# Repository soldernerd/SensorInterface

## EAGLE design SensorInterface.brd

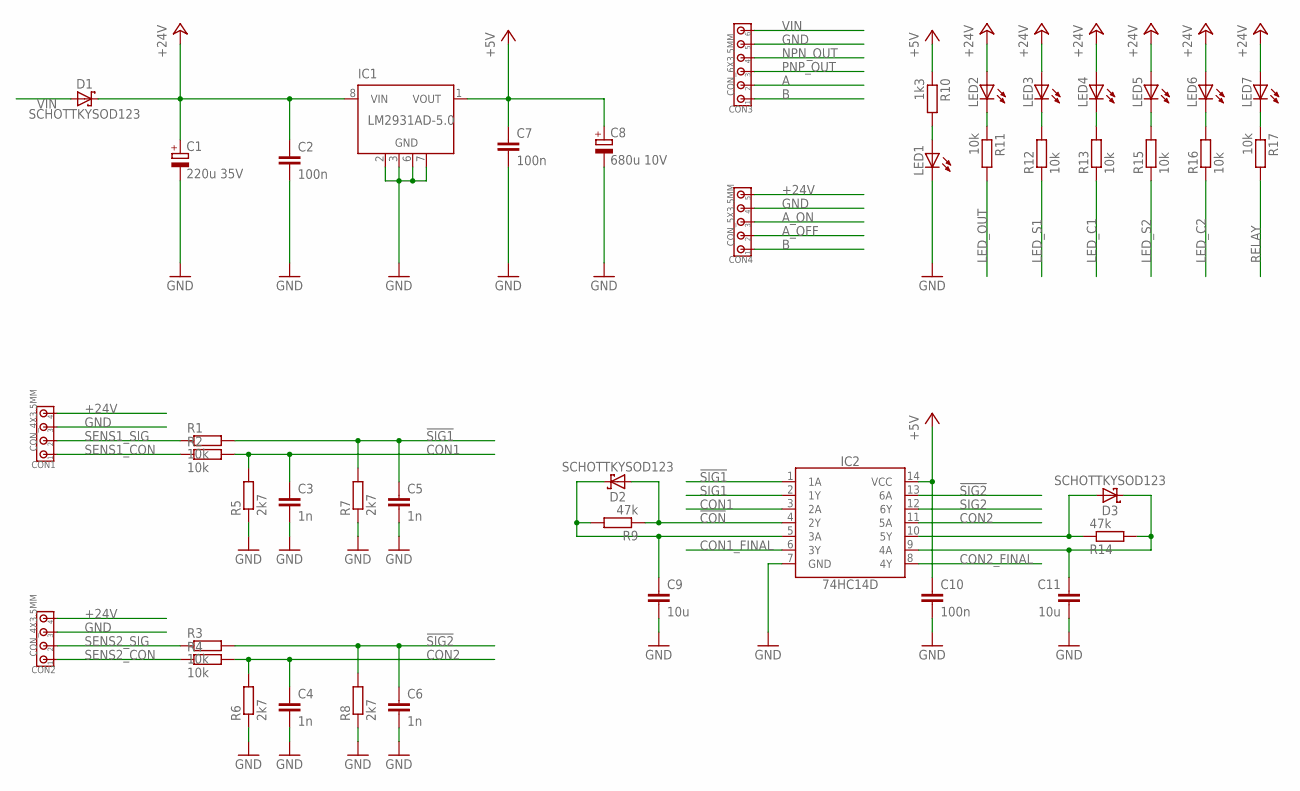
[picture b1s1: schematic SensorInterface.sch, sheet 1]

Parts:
C1: 220u 35V; 8MM
C2, C7, C10: 100n; C0805
C3, C4, C5, C6: 1n; C0805
C8: 680u 10V; 8MM
C9, C11: 10u; C0805
CON1, CON2: CON_4X3.5MM; 3.5MM_4X
CON3: CON_6X3.5MM; 3.5MM_6X
CON4: CON_5X3.5MM; 3.5MM_5X
D1, D2, D3: SCHOTTKYSOD123; SOD123
IC1: LM2931AD-5.0; SOIC8
IC2: 74HC14D; SO14
LED1, LED2, LED3, LED4, LED5, LED6, LED7: LED0805_NB; LED0805_NOBOARDER
R1, R2, R3, R4, R11, R12, R13, R15, R16, R17: 10k; R0805
R5, R6, R7, R8: 2k7; R0805
R9, R14: 47k; R0805
R10: 1k3; R0805

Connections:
!CON!: D2.A, IC2.4 (2Y), R9.1
!CON!1: D3.A, IC2.10 (5Y), R14.1
!SIG1!: C5.1, IC2.1 (1A), R1.2, R7.2; also elsewhere on the board
!SIG2!: C6.1, IC2.13 (6A), R3.2, R8.2; also elsewhere on the board
+5V: C7.1, C8.+, C10.1, IC1.1 (VOUT), IC2.14 (VCC), R10.1; also elsewhere on the board
+24V: C1.+, C2.1, CON1.4, CON2.4, CON4.5, D1.C, IC1.8 (VIN), LED2.A, LED3.A, LED4.A, LED5.A, LED6.A, LED7.A; also elsewhere on the board
A: CON3.2; also elsewhere on the board
A_OFF: CON4.2; also elsewhere on the board
A_ON: CON4.3; also elsewhere on the board
B: CON3.1, CON4.1
CON1: C3.1, IC2.3 (2A), R2.2, R5.2
CON1_FINAL: IC2.6 (3Y); also elsewhere on the board
CON2: C4.1, IC2.11 (5A), R4.2, R6.2
CON2_FINAL: IC2.8 (4Y); also elsewhere on the board
GND: C1.-, C2.2, C3.2, C4.2, C5.2, C6.2, C7.2, C8.-, C9.2, C10.2, C11.2, CON1.3, CON2.3, CON3.5, CON4.4, IC1.2 (GND), IC1.3 (GND), IC1.6 (GND), IC1.7 (GND), IC2.7 (GND), LED1.C, R5.1, R6.1, R7.1, R8.1; also elsewhere on the board
LED_C1: R13.1; also elsewhere on the board
LED_C2: R16.1; also elsewhere on the board
LED_OUT: R11.2; also elsewhere on the board
LED_S1: R12.1; also elsewhere on the board
LED_S2: R15.1; also elsewhere on the board
unnamed: C11.1, D3.C, IC2.9 (4A), R14.2
unnamed: C9.1, D2.C, IC2.5 (3A), R9.2
unnamed: LED1.A, R10.2
unnamed: LED2.C, R11.1
unnamed: LED7.C, R17.1
unnamed: LED6.C, R16.2
unnamed: LED5.C, R15.2
unnamed: LED4.C, R13.2
unnamed: LED3.C, R12.2
NPN_OUT: CON3.4; also elsewhere on the board
PNP_OUT: CON3.3; also elsewhere on the board
RELAY: R17.2; also elsewhere on the board
SENS1_CON: CON1.1, R2.1
SENS1_SIG: CON1.2, R1.1
SENS2_CON: CON2.1, R4.1
SENS2_SIG: CON2.2, R3.1
SIG1: IC2.2 (1Y); also elsewhere on the board
SIG2: IC2.12 (6Y); also elsewhere on the board
VIN: CON3.6, D1.A

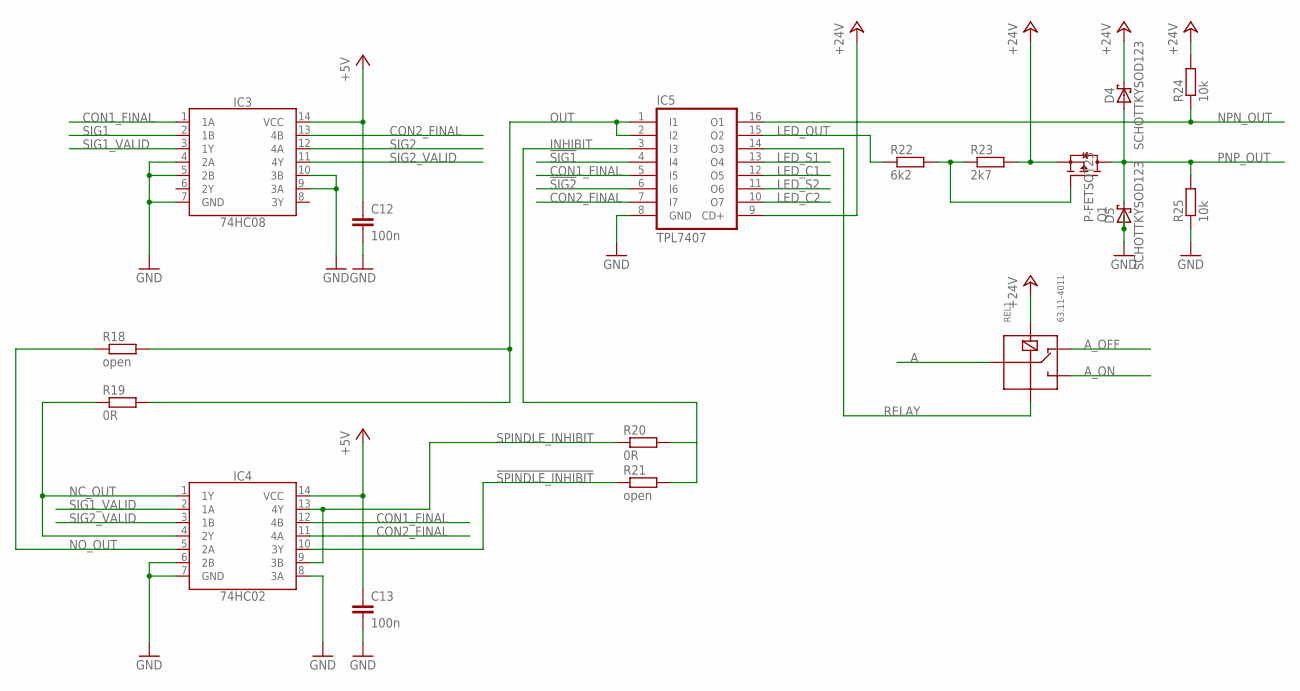
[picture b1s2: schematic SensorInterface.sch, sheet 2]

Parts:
C12, C13: 100n; C0805
D4, D5: SCHOTTKYSOD123; SOD123
IC3: 74HC08; SO14
IC4: 74HC02; SO14
IC5: TPL7407; SO16
Q1: P-FETSOT23; SOT23
R18, R21: open; R0805
R19, R20: 0R; R0805
R22: 6k2; R0805
R23: 2k7; R0805
R24, R25: 10k; R0805
REL1: 63.11-4011; G5LE

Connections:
!SIG1!: IC5.4 (I4); also elsewhere on the board
!SIG2!: IC5.6 (I6); also elsewhere on the board
!SPINDLE_INHIBIT!: IC4.10 (3Y), R21.1
+5V: C12.1, C13.1, IC3.14 (VCC), IC4.14 (VCC); also elsewhere on the board
+24V: D4.C, IC5.9 (CD+), Q1.2 (S), R23.2, R24.2, REL1.2; also elsewhere on the board
A: REL1.COM; also elsewhere on the board
A_OFF: REL1.O; also elsewhere on the board
A_ON: REL1.C; also elsewhere on the board
CON1_FINAL: IC3.1 (1A), IC4.12 (4B), IC5.5 (I5); also elsewhere on the board
CON2_FINAL: IC3.13 (4B), IC4.11 (4A), IC5.7 (I7); also elsewhere on the board
GND: C12.2, C13.2, D5.A, IC3.4 (2A), IC3.5 (2B), IC3.7 (GND), IC3.9 (3A), IC3.10 (3B), IC4.6 (2B), IC4.7 (GND), IC4.8 (3A), IC5.8 (GND), R25.1; also elsewhere on the board
INHIBIT: IC5.3 (I3), R20.2, R21.2
LED_C1: IC5.12 (O5); also elsewhere on the board
LED_C2: IC5.10 (O7); also elsewhere on the board
LED_OUT: IC5.15 (O2), R22.1; also elsewhere on the board
LED_S1: IC5.13 (O4); also elsewhere on the board
LED_S2: IC5.11 (O6); also elsewhere on the board
unnamed: Q1.1 (G), R22.2, R23.1
NC_OUT: IC4.1 (1Y), IC4.4 (2Y), R19.1
NO_OUT: IC4.5 (2A), R18.1
NPN_OUT: IC5.16 (O1), R24.1; also elsewhere on the board
OUT: IC5.1 (I1), IC5.2 (I2), R18.2, R19.2
PNP_OUT: D4.A, D5.C, Q1.3 (D), R25.2; also elsewhere on the board
RELAY: IC5.14 (O3), REL1.1; also elsewhere on the board
SIG1: IC3.2 (1B); also elsewhere on the board
SIG1_VALID: IC3.3 (1Y), IC4.2 (1A)
SIG2: IC3.12 (4A); also elsewhere on the board
SIG2_VALID: IC3.11 (4Y), IC4.3 (1B)
SPINDLE_INHIBIT: IC4.9 (3B), IC4.13 (4Y), R20.1

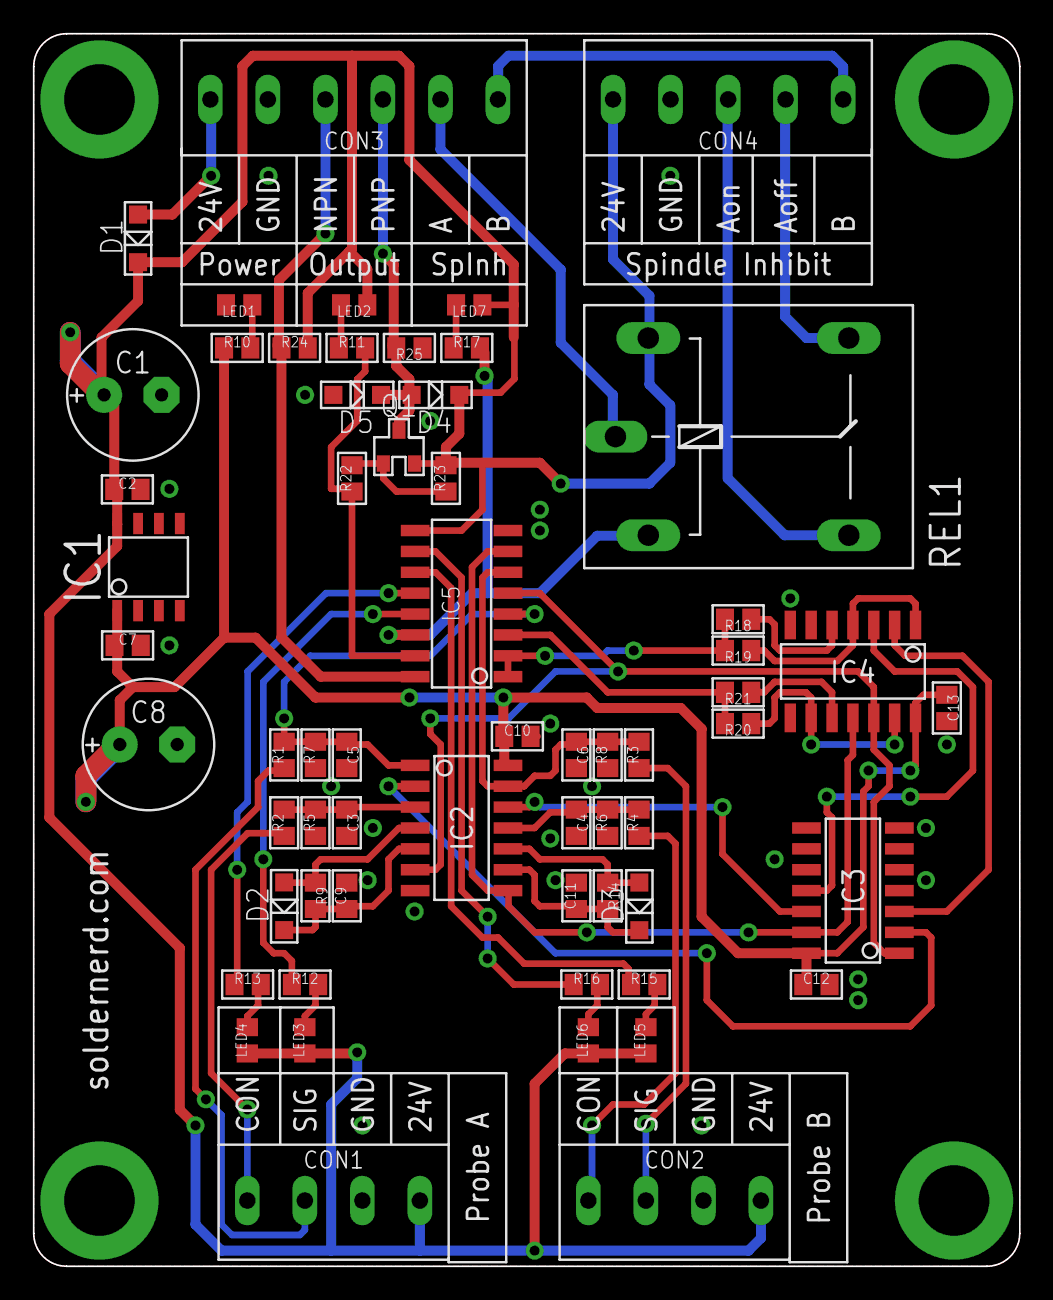
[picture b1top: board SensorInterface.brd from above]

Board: 2 copper layers, 60.0 x 75.0 mm, 61 parts (0 on the bottom side), 48 nets.

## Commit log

2020-12-08 Initial commit but fully functional
